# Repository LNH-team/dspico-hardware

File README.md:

# DSpico Hardware
## 🗺️ Contents
- [ℹ Introduction](#ℹ-introduction)
- [❔ About this repository](#-about-this-repository).
- [🎮 DSpico PCB](#-dspico-pcb)
- [🧰 DSpico Shell](#-dspico-shell)
- [🎨 Artwork: Stickers and box art](#-artwork-stickers-and-box-art)
- [📦 Instructions](#-instructions)
- [🛠 Development](#-development)
- [👥 Contributions](#-contributions)
- [👾 Discord](#-discord)
- [📋 LNH Team Statement](#-lnh-team-statement)
- [⚖ License](#-license)

## ℹ Introduction
### What is DSpico?
DSpico is the world's first open-source DS(i) flashcart, created by the LNH team. Everything from the PCB, shell, stickers, and box art is open-source. You can either build it yourself as a DIY project or have it made by a manufacturer.

### Features
- RP2040 microcontroller
- 16 Mbit flash memory
- Micro USB port
- Micro SD slot
- Development port
- Two LEDs (red and blue)
- Dual power support: can be powered by USB and DS simultaneously (by ORing circuit)

With the [DSpico Firmware](https://github.com/LNH-team/dspico-firmware):
- Sequential SD read speed: up to 6MB/s
- Power consuption: ~57 mW
- Compatible with DSi mode
- Compatible with [Pico Loader](https://github.com/LNH-team/pico-loader) and [Pico Launcher](https://github.com/LNH-team/pico-launcher)

## ❔ About this repository
This repository contains the necessary files for the hardware of the DSpico, including a PCB, CAD design of the shell, stickers for cartridge and box art.

## 🎮 DSpico PCB
The PCB design is located in the [`dspico-pcb`](dspico-pcb) folder. This folder contains all the necessary files for PCB fabrication, as well as the design files created using the electronic design software.

### 📂 Included Subfolders:
- [`design-files`](dspico-pcb/design-files): PCB schematic and layout of DSpico. (KiCad format)
- [`fabrication-files`](dspico-pcb/fabrication-files): Gerber files, Pick&Place files and BOM for PCB fabrication of DSpico.
- [`docs`](dspico-pcb/docs): Documentation for manufacturing and assembling DSpico.

### 🔌 Pinout

| **Peripheral**  | **Pin name - Peripheral** | **Pin name - RP2040** | **Pin number - RP2040** |
|-------------|-----------------------|-------------------|-------------|
| **DS Slot** | D0                    | GPIO12            | 15          |
|             | D1                    | GPIO13            | 16          |
|             | D2                    | GPIO14            | 17          |
|             | D3                    | GPIO15            | 18          |
|             | D4                    | GPIO16            | 27          |
|             | D5                    | GPIO17            | 28          |
|             | D6                    | GPIO18            | 29          |
|             | D7                    | GPIO19            | 30          |
|             | CLK_DS                | GPIO11            | 14          |
|             | ROM_CS                | GPIO10            | 13          |
|             | SPI_CS                | GPIO21            | 32          |
|             | IRQ                   | GPIO20            | 31          |
|             | RST_DS                | GPIO09            | 12          |
| **SD slot**| CLK_SD                | GPIO03            | 5           |
|             | DAT0                  | GPIO05            | 7           |
|             | DAT1                  | GPIO06            | 8           |
|             | DAT2                  | GPIO07            | 9           |
|             | DAT3                  | GPIO08            | 11          |
|             | CMD                   | GPIO04            | 6           |
| **DEV port**| SWD                   | SWD               | 25          |
|             | SWCLK                 | SWCLK             | 24          |
|             | TX                    | GPIO0            | 2           |
|             | RX                    | GPIO1            | 3           |
| **Blue LED**   | LED_B                 | GPIO28            | 40          |
| **Red LED**   | LED_R                 | GPIO27            | 39          |

## 🧰 DSpico Shell

The CAD design of the shell is located in the [`dspico-shell`](dspico-shell) folder. This folder contains 3D models of the shell (output 3d models and design files), which can be viewed and modified using CAD design software Autodesk Inventor

### 📂 Included Subfolders:
- [`design-files`](dspico-shell/design-files): Contains source design files for the shell
- [`3d-models`](dspico-shell/3d-models): Contains 3D models of the shell in STL and STEP format for fabrication.

## 🎨 Artwork: Stickers and box art
The stickers and box art design are located in the [`dspico-artwork-design`](dspico-artwork-design).  This folder contains stickers for cartridge and box art in SVG, PSD and PNG formats.

### 📂 Included Subfolders:
- [`stickers`](dspico-artwork-design/stickers): Stickers to print and put on your DSpico cartridge.
- [`box-art`](dspico-artwork-design/box-art): Box art design to print and put on your DS box.
- [`logo`](dspico-artwork-design/logo): DSpico logo in different formats.
- [`others`](dspico-artwork-design/others): Other graphics related to DSpico

## 📦 Instructions
### 1️⃣ Build
1. **Manufacture the PCB and Shell**<br>
    Start by producing both the PCB and the shell. Go to the respective sections, [`dspico-pcb`](dspico-pcb) and [`dspico-shell`](dspico-shell), and read the README file in each to understand how to create these parts.

2. **Optional: Customize with a Sticker and Box Art**<br>
    If desired, you can print a sticker from the stickers section and add box art [`dspico-artwork-design`](dspico-artwork-design) for storing your DSpico (for example, by reusing an existing box).

### 2️⃣ Assembly
Once you have both the PCB and the shell manufactured, the next step is to assemble them. Follow these steps:
1. First, insert the PCB into the bottom part of the shell.
2. Next, attach the top part of the shell by aligning the pegs with the holes in the bottom part.
3. Stick your favorite DSpico sticker on top part.
Make sure everything fits, and your DSpico will be ready for the next steps!

### 3️⃣ Setup the software
Follow the [guide](https://github.com/LNH-team/dspico/blob/develop/GUIDE.md) for instructions on how to compile and setup the firmware and the contents of the micro SD card.

## 🛠 Development
The DSpico features a development port for creating new applications and developing new peripherals. The available communication ports are as follows:
- UART
- I2C
- x2 GPIO
- SWD (debug)

As for the power it can provide to peripherals, it is:
- 3.3 V (up to 50 mA)

The pitch between pins of this port is 2.54 mm such that some connectors can be soldered (as long as it does not interfere with the rest of the DSpico mechanics). For example a male or female header.

## 👥 Contributions

Contributions are welcome. If you wish to improve the PCB or shell designs, feel free to submit a pull request!

### Contributors:

#### PCB:
 - [nitehack](https://www.github.com/nitehack)
 - [Gericom](https://github.com/Gericom) (first DSpico prototype)

#### Shell:
 - rcuevas
 - [nitehack](https://www.github.com/nitehack)

#### Artworks:
 - [nitehack](https://www.github.com/nitehack)

## 👾 Discord
- [DS⁽ⁱ⁾ Mode Hacking!](https://discord.gg/fCzqcWteC4)

## 📋 LNH Team Statement
We wish to make it clear that the LNH team has no affiliation with any commercial projects, and we do not endorse or engage in any for-profit endeavors concerning DSpico or related materials. This statement serves as a formal disavowal of any financial or business dealings that may arise in relation to DSpico, and we take no responsibility for any actions or transactions carried out by third parties in this regard.

## ⚖ License

This project is licensed under the CC BY-SA 4.0 License. See the [`LICENSE`](LICENSE) file for more details.

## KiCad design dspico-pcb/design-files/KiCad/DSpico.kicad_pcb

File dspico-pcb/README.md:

# DSpico PCB

This repository contains the files and configurations needed to fabricate and assemble the PCB for the **DSpico** flashcart. You can manufacture with the manufacturer you prefer. In this readme we include a guide on how to order it from [JLCPCB](https://cart.jlcpcb.com/quote?spm=Jlcpcb.Homepage.1006)

## 📂 Included Subfolders:
- [`design-files`](./design-files): PCB schematic and layout of DSpico. (KiCad format)
- [`fabrication-files`](./fabrication-files): Gerber files, Pick&Place files and BOM for PCB fabrication of DSpico.
   - 📂 `Gerber`: Gerber files required for fabrication.
   - 📂 `NC Drill`: Contains the NC Drill files required for PCB hole drilling.
   - 📂 `BOM`: Bill of Materials (BOM) for assembly.
   - 📂 `Pick Place`: Pick and Place files for component placement.
- [`docs`](./docs): Documentation for manufacturing and assembling DSpico. (including schematics)

---

## 📦 Guide to get a PCB

### 1. PCB Order- JLCPCB
> [!WARNING]
> This guide was last reviewed on **November 22, 2025**. 
> Please be aware that the manufacturer's website and production processes may have changed since this date. 

1. **Prepare files**
   - Make a compressed file ZIP of `NC Drill` and `Gerber` folder with the name of `Gerber.zip` (for example)
2. **Go to the Website of manufacturer**
  
   - Visit [JLCPCB PCB Quote](https://cart.jlcpcb.com/quote).

3. **Upload Gerber and NC Drill Files**:

   - Upload the `Gerber.zip` file to the JLCPCB configurator.

4. **PCB Configuration**

   - Base Material: **FR-4**
   - Number of Layers: **4 layers** (auto-detected after uploading Gerber files).
   - Dimensions: (auto-detected after uploading Gerber files).
   - Quantity: **5 units** (minimum)

>PCB Specifications
   - Deburring/Edge rounding: Yes
   - Different Design: 1
   - Delivery Format : Single PCB
   - PCB Thickness: **0.8mm** (very important)
   - PCB Color: (As you want but normally green is the cheapest)
   - Silkscreen: **White** 
   - Material Type: FR4 TG135
   - Surface Finish: **ENIG**
   - Gold Thickness: **1U"**. (Or more, but more expensive)

>High-spec Options
   - Outer Copper Weight: **1 oz**
   - Inner Copper weight: **0.5 oz**
   - Specify Layer Sequence: YES

   - Specify Stackup: **No**
   - Via Covering: **Plugged**
   - Min via hole size/diameter: **0.3mm (0.4/0.45mm)**
   - Board Outline Tolerance: **±0.2mm (Regular)**
   - Confirm Production File: **Yes**
   - Mark on PCB: **Remove Mark**
   - Electrical Test: **Flying Probe Fully Test**
   - Gold Fingers: **No**
   - Castellated Holes: **No**
   - Press-Fit Holes: **No**
   - Edge Plating: **No**
   - Blind Slots: **No**
   - UL Marking: **No**
   - Via Plating Method: **Not Specified** 

>PCB Remark
>
Add the next note:

**Ensure enough space is left on the edge rails for the USB connector. Leave the slot space as per the silkscreen**

If they contact you via email after placing the order about this note, attach the following image

---

### 2. PCB Assembly Order- first step - JLCPCB

1. **Assembly Type**:
   - **Assemble top side**.
   - PCBA Type: **Standard**
   - Assembly Side: **Top side**
   - PCBA Qty: **5**. (Or custom Qty)
   - Edge Rails/Fiducials: **Added by JLCPCB**
   - Confirm Parts Placement: **Yes**
   - Stencil Storage: **No**
   - Fixture Storage: **No**
   - Parts Selection: **By Customer**

2. **Advanced Options**:
   - Bake Components: **No**
   - Board Cleaning: **Yes**
   - Packaging: **Antistatic bubble film**.
   - Solder Paste: **SN96.5%, Ag3.0%, Cu0.5%(260ºC)**
   - Add paste for unpopulated pad & step stencil opening: **No**
   - Function test: **No** 
   - Photo confirmation: **No**
   - Conformal Coating (cleaning included): **No**
   - Depanel boards & edge rail before delivery: **No**
   - Flying Probe Test: **No**
   - Nitrogen reflow soldering: **No**
   - PCBA remark: **No**

3. On the **Price Summary** window, click **Next**.

---

### 3. PCB Assembly Order - second step - JLCPCB

Follow these steps to continue with the process

### Preview pcb specifications
On the **Preview PCB** page, click **Next** to proceed.  

### Add Required Files for assembly 
In the next window, upload the necessary files for your DSpico PCB:  

   1. **Add BOM File**  
      - Click on **Add BOM File**.  
      - Search for and select the Bill of Materials (BOM) file:  
        - `"Bill of Materials-DSpico.xlsx"` (Ensure it matches the version of DSpico you are building).  

   2. **Add Pick-and-Place (CPL) File**  
      - Click on **Add CPL File**.  
      - Search for and select the Pick and Place file:  
        - `"Pick Place for DSpico_PCB.csv"` (Ensure it matches the version of DSpico you are building).  

   3. Once both files are uploaded, press **Process BOM & CPL**.  

### Verify Components  
In the next window, carefully verify the components:  

1. Check that each component selected by the **JLCPCB tool** matches the corresponding part in the BOM:  
   - Use the file `"Bill of Materials-DSpico.xlsx"` for reference.  
   - Ensure the selected part is the same or a suitable alternative.  

     (The image is just a reference, please follow the components indicated in the BOM file)

> [!IMPORTANT]
> If the components do not match, there is a risk of malfunction or improper operation of the DSpico. **Double-check every part detail carefully. It's your responsibility**  

> [!TIP]  
 > JLCPCB may sometimes show certain parts as out of stock. However, other users may have that part in their accounts, which you can purchase and add to your order. If this is not an option, you can place an order for the part separately, though you’ll need to wait for JLCPCB to buy them and receive them.  After using the necessary components, you can sell your parts on your account. More info: https://jlcpcb.com/help/article/What-is-JLCPCB-Parts-Pre-order-Service
 > You can also look for an alternative to the component by clicking the magnifying-glass icon next to it and searching for a compatible replacement.

### Check Component Placement  
1. In the next window, verify the component placement:  
   - Ensure the **position**, **rotation**, and **Pin 1 orientation** are correct.  

### 3. Finalize the Process  
1. Click **Next** to proceed through the final steps of the process.  
2. Wait for JLCPCB to review your order.  
3. Review and accept their feedback before making the payment.  

--- 

## 💡 Recommendations
- We recommend using a **Hard Gold** surface finish if you can afford it. This is not possible with JLCPCB, but it is available with PCBWAY and other manufacturers. It will significantly improve the conductivity of the PCB pins, reducing detection issues with the DSpico.

## ❓ FAQ
>- Can I order just 1 PCB assembled?

Depending on the manufacturer, you may or may not be able to do this, but it will be very expensive. They usually ask for a minimum of 2 assembled PCBs. We recommend ordering 5 assembled PCBs.

>- What happens if a component of JLCPCB is out of stock? 

You must find an alternative or purchase that component from the JLCPCB library. See here for more information: https://jlcpcb.com/help/article/What-is-JLCPCB-Parts-Pre-order-Service

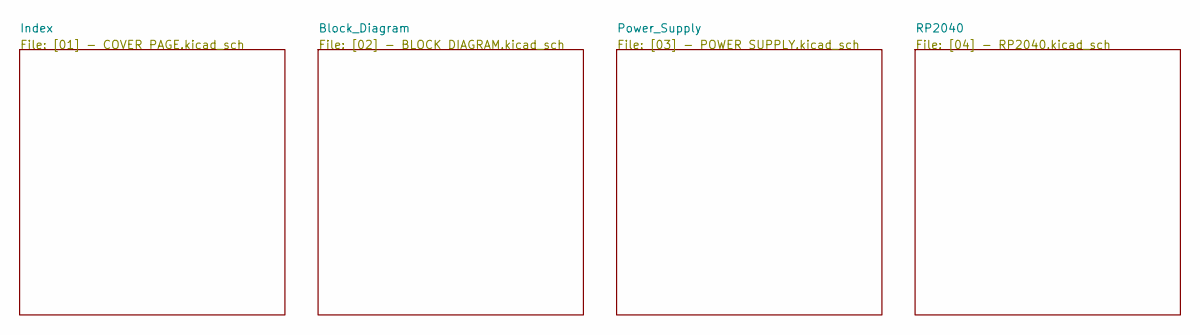
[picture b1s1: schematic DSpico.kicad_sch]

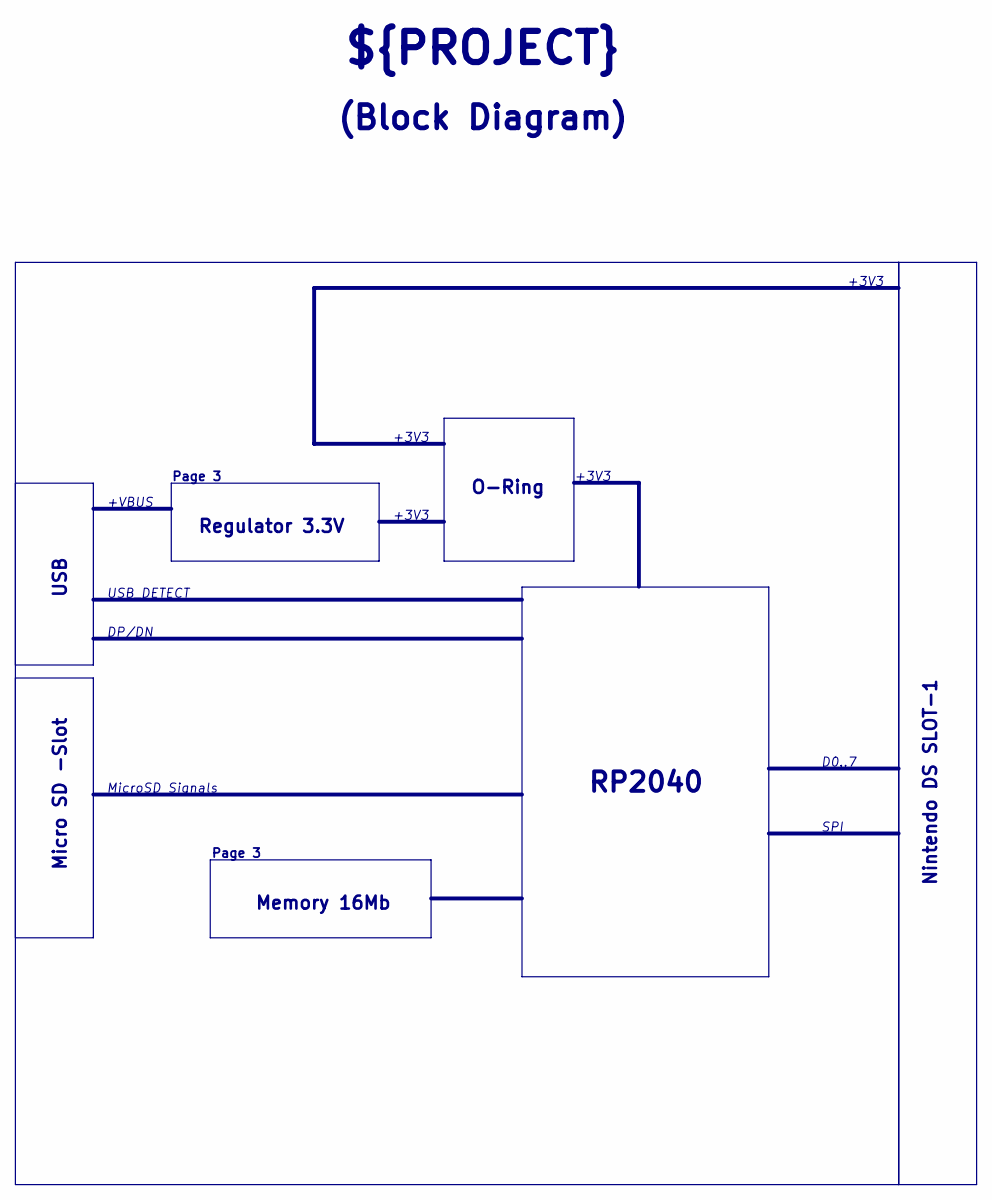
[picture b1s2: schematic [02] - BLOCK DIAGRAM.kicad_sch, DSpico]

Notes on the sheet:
+VBUS
+3V3
RP2040
Page 3
(Block Diagram)
USB_DETECT
D0..7
SPI
O-Ring
USB
MicroSD Signals
Regulator 3.3V
Nintendo DS SLOT-1
DP/DN
${PROJECT}
Micro SD -Slot
Memory 16Mb

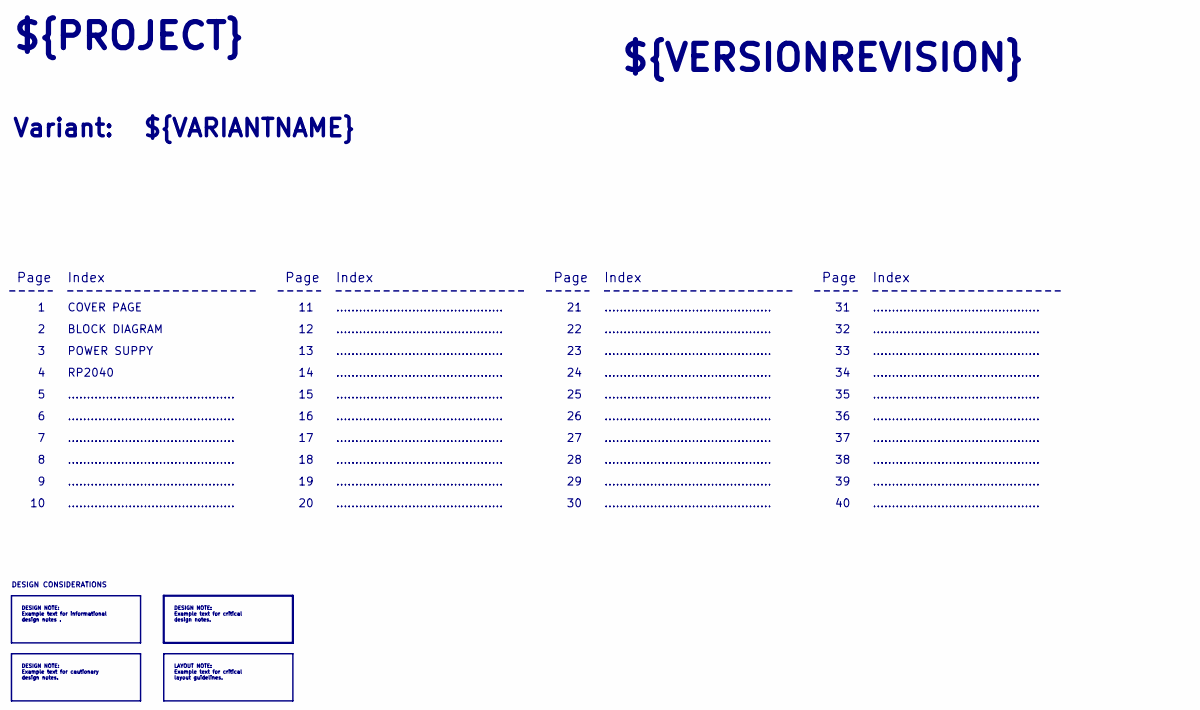
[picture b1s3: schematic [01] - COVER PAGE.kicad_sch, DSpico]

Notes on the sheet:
Page
............................................
POWER SUPPY
COVER PAGE
${VARIANTNAME}
Index
BLOCK DIAGRAM
${PROJECT}
DESIGN CONSIDERATIONS
RP2040
${VERSIONREVISION}
Variant:
DESIGN NOTE: Example text for cautionary design notes.
DESIGN NOTE: Example text for informational design notes .
DESIGN NOTE: Example text for critical design notes.
LAYOUT NOTE: Example text for critical layout guidelines.

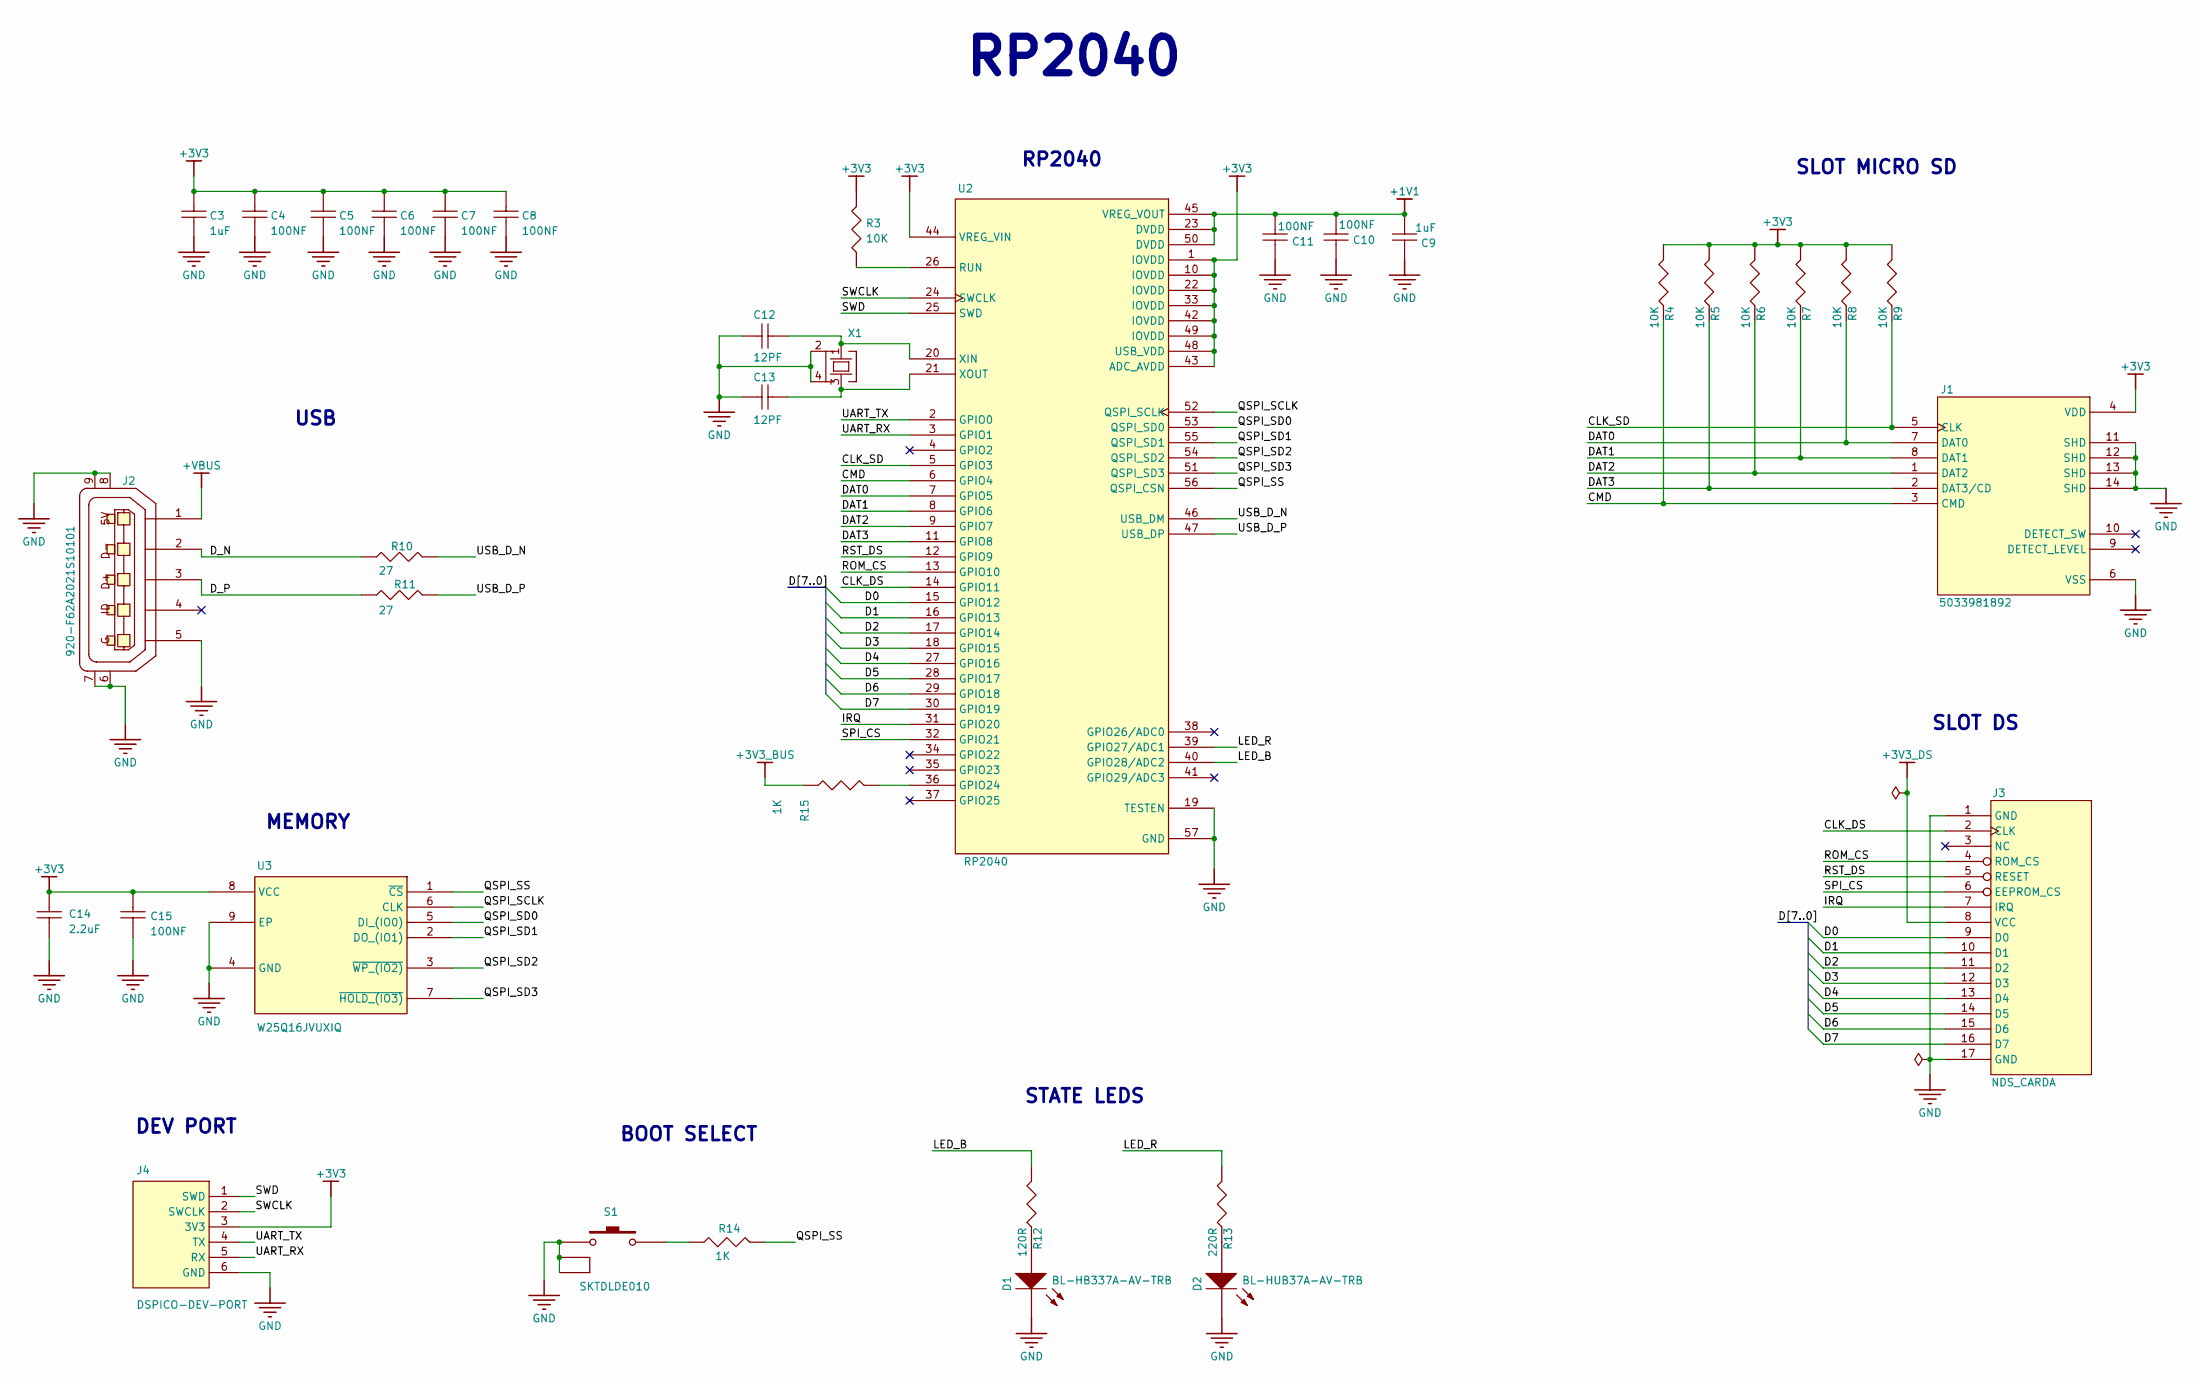
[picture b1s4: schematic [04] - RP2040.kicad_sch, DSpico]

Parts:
C3, C9: 1uF; C0402; TOLERANCE 10%; VOLTAGE RATING 25V; MANUFACTURER PART NUMBER C1005X5R1E105K050BC
C4, C5, C6, C7, C8, C10, C11, C15: 100NF; C0402; TOLERANCE 10%; VOLTAGE RATING 16V; MANUFACTURER PART NUMBER GRM155R71C104KA88D
C12, C13: 12PF; C0402; TOLERANCE 5%; VOLTAGE RATING 50V; MANUFACTURER PART NUMBER 04025A120JAT2A
C14: 2.2uF; C0402; MANUFACTURER PART NUMBER C1005X5R1A225K050BC
D1: BL-HB337A-AV-TRB; LED0402-RD; FORWARD VOLTAGE 2.8V; MANUFACTURER PART NUMBER BL-HB337A-AV-TRB
D2: BL-HUB37A-AV-TRB; LED0402-RD; FORWARD VOLTAGE 2V; MANUFACTURER PART NUMBER BL-HUB37A-AV-TRB
J1: 5033981892; 503398-1892_MOL
J2: 920-F62A2021S10101; MICRO-USB_MICRO-USB-31
J3: NDS_CARDA; NDS_CARD
J4: DSPICO-DEV-PORT; EP_DEV_PORT; CURRENT RATING ?; VOLTAGE RATING 3.3V; MANUFACTURER PART NUMBER PICO-DEVELOP-PORT
R3, R4, R5, R6, R7, R8, R9: 10K; R0402; TOLERANCE 1%; POWER RATING 63mW; MANUFACTURER PART NUMBER CRCW040210K0FKED
R10, R11: RC0402FR-0727RL; R0402; WORKING VOLTAGE 50V; TOLERANCE 1%
R12: 120R; R0402; VOLTAGE RATING 50V; POWER RATING 62.5mW; MANUFACTURER PART NUMBER RC0402FR-07120RL
R13: 220R; R0402; VOLTAGE RATING 50V; POWER RATING 62.5mW; MANUFACTURER PART NUMBER RC0402FR-07220RL
R14, R15: 1K; R0402; TOLERANCIA DE RESISTENC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 ± 1%; MANUFACTURER PART NUMBER CRCW04021K00FKED
S1: SKTDLDE010; KEY-SMD_SKTDLDE010; MANUFACTURER PART NUMBER SKTDLDE010
U2: RP2040; QFN40P700X700X90-57N
U3: W25Q16JVUXIQ; SON50P300X200X60-9N
X1: XYDBPCNANF-12MHZ; OSC-SMD_4P-L2.5-W2.0-BL

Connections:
+1V1: C9.2, C10.2, C11.2, U2.23 (DVDD), U2.45 (VREG_VOUT), U2.50 (DVDD)
+3V3: C3.2, C4.2, C5.2, C6.2, C7.2, C8.2, C14.2, C15.2, J1.4 (VDD), J4.3 (3V3), R3.2, R4.2, R5.2, R6.2, R7.2, R8.2, R9.2, U2.1 (IOVDD), U2.10 (IOVDD), U2.22 (IOVDD), U2.33 (IOVDD), U2.42 (IOVDD), U2.43 (ADC_AVDD), U2.44 (VREG_VIN), U2.48 (USB_VDD), U2.49 (IOVDD), U3.8 (VCC); also elsewhere on the board
+3V3_BUS: R15.1; also elsewhere on the board
+3V3_DS: J3.8 (VCC); also elsewhere on the board
+VBUS: J2.1; also elsewhere on the board
/RP2040/CLK_DS: J3.2 (CLK), U2.14 (GPIO11)
/RP2040/CLK_SD: J1.5 (CLK), R9.1, U2.5 (GPIO3)
/RP2040/CMD: J1.3 (CMD), R4.1, U2.6 (GPIO4)
/RP2040/D0: J3.9 (D0), U2.15 (GPIO12)
/RP2040/D1: J3.10 (D1), U2.16 (GPIO13)
/RP2040/D2: J3.11 (D2), U2.17 (GPIO14)
/RP2040/D3: J3.12 (D3), U2.18 (GPIO15)
/RP2040/D4: J3.13 (D4), U2.27 (GPIO16)
/RP2040/D5: J3.14 (D5), U2.28 (GPIO17)
/RP2040/D6: J3.15 (D6), U2.29 (GPIO18)
/RP2040/D7: J3.16 (D7), U2.30 (GPIO19)
/RP2040/DAT0: J1.7 (DAT0), R8.1, U2.7 (GPIO5)
/RP2040/DAT1: J1.8 (DAT1), R7.1, U2.8 (GPIO6)
/RP2040/DAT2: J1.1 (DAT2), R6.1, U2.9 (GPIO7)
/RP2040/DAT3: J1.2 (DAT3/CD), R5.1, U2.11 (GPIO8)
/RP2040/D_N: J2.2, R10.1
/RP2040/D_P: J2.3, R11.1
/RP2040/IRQ: J3.7 (IRQ), U2.31 (GPIO20)
/RP2040/LED_B: R12.2, U2.40 (GPIO28/ADC2)
/RP2040/LED_R: R13.2, U2.39 (GPIO27/ADC1)
/RP2040/QSPI_SCLK: U2.52 (QSPI_SCLK), U3.6 (CLK)
/RP2040/QSPI_SD0: U2.53 (QSPI_SD0), U3.5 (DI_(IO0))
/RP2040/QSPI_SD1: U2.55 (QSPI_SD1), U3.2 (DO_(IO1))
/RP2040/QSPI_SD2: U2.54 (QSPI_SD2), U3.3 (~WP_(IO2))
/RP2040/QSPI_SD3: U2.51 (QSPI_SD3), U3.7 (~HOLD_(IO3))
/RP2040/QSPI_SS: R14.2, U2.56 (QSPI_CSN), U3.1 (~CS)
/RP2040/ROM_CS: J3.4 (ROM_CS), U2.13 (GPIO10)
/RP2040/RST_DS: J3.5 (RESET), U2.12 (GPIO9)
/RP2040/SPI_CS: J3.6 (EEPROM_CS), U2.32 (GPIO21)
/RP2040/SWCLK: J4.2 (SWCLK), U2.24 (SWCLK)
/RP2040/SWD: J4.1 (SWD), U2.25 (SWD)
/RP2040/UART_RX: J4.5 (RX), U2.3 (GPIO1)
/RP2040/UART_TX: J4.4 (TX), U2.2 (GPIO0)
/RP2040/USB_D_N: R10.2, U2.46 (USB_DM)
/RP2040/USB_D_P: R11.2, U2.47 (USB_DP)
GND: C3.1, C4.1, C5.1, C6.1, C7.1, C8.1, C9.1, C10.1, C11.1, C12.1, C13.1, C14.1, C15.1, D1.1, D2.1, J1.6 (VSS), J1.11 (SHD), J1.12 (SHD), J1.13 (SHD), J1.14 (SHD), J2.5, J2.6, J2.7, J2.8, J2.9, J3.1 (GND), J3.17 (GND), J4.6 (GND), S1.1, S1.3, S1.4, U2.19 (TESTEN), U2.57 (GND), U3.4 (GND), U3.9 (EP), X1.2, X1.4; also elsewhere on the board
unnamed: D1.2, R12.1
unnamed: D2.2, R13.1
unnamed: R14.1, S1.2
unnamed: R15.2, U2.36 (GPIO24)
unnamed: R3.1, U2.26 (RUN)
unnamed: C12.2, U2.20 (XIN), X1.1
unnamed: C13.2, U2.21 (XOUT), X1.3

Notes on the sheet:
SLOT MICRO SD
MEMORY
BOOT SELECT
RP2040
SLOT DS
STATE LEDS
DEV PORT
USB

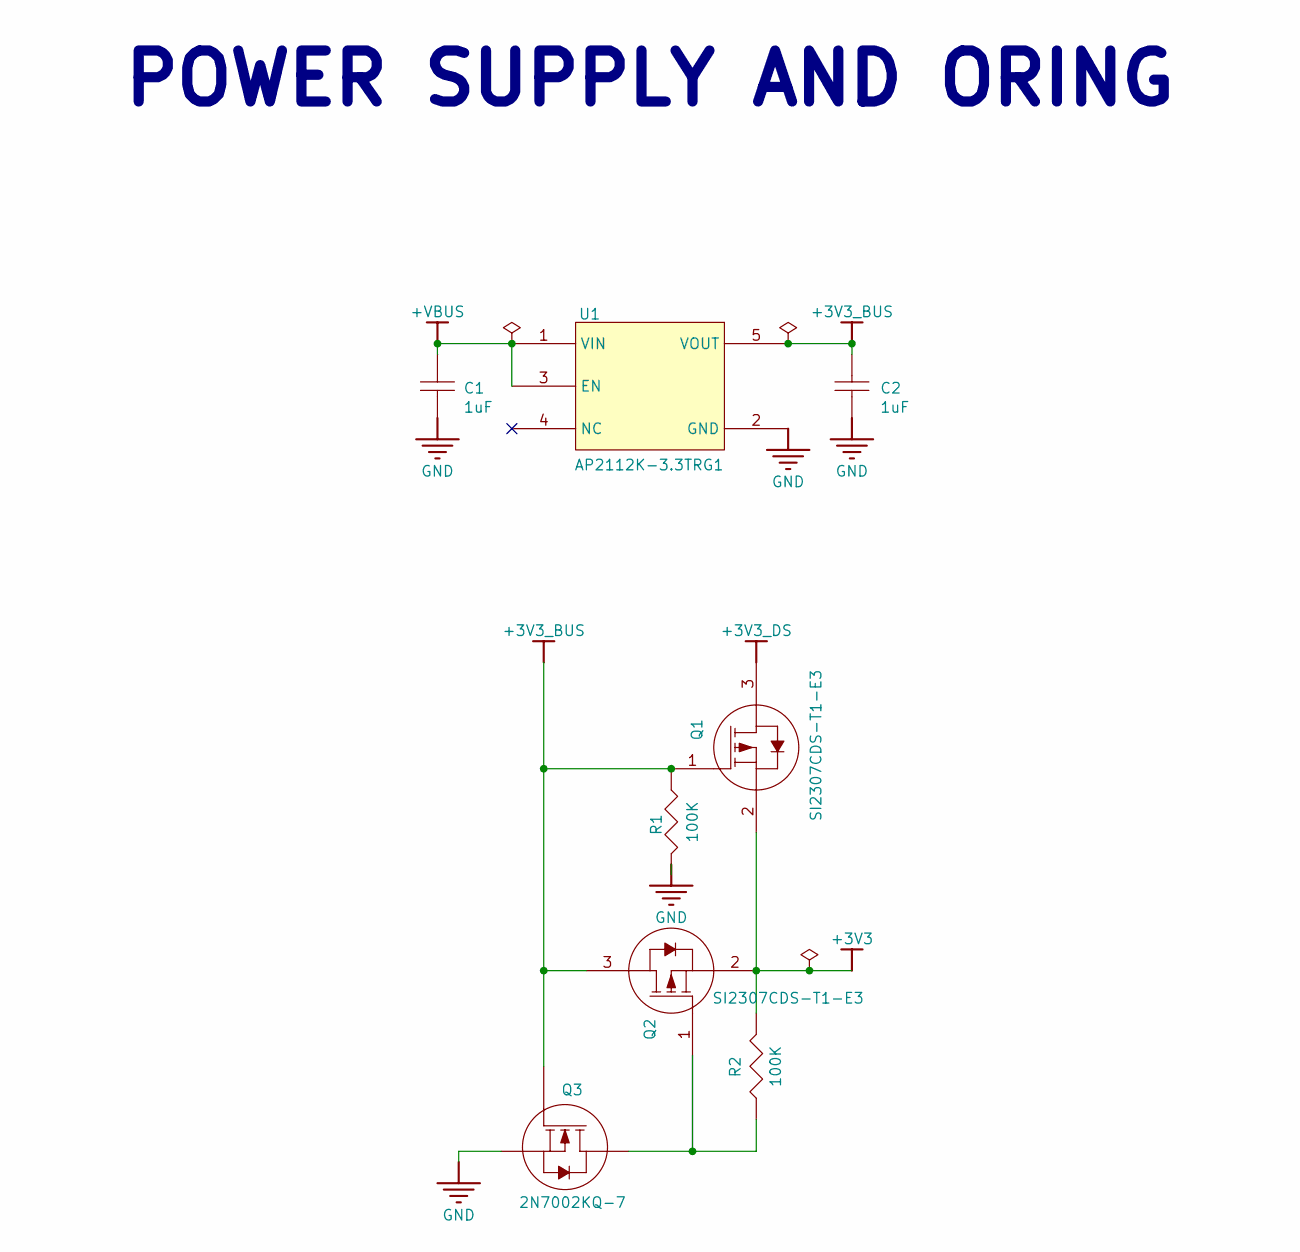
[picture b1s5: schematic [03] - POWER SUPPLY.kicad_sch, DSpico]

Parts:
C1, C2: 1uF; C0402; TOLERANCE 10%; VOLTAGE RATING 25V; MANUFACTURER PART NUMBER C1005X5R1E105K050BC
Q1, Q2: SI2307CDS-T1-E3; SOT-23_L2.9-W1.3-P1.90-LS2.4-BR
Q3: 2N7002KQ-7; SOT-23_L2.9-W1.3-P1.90-LS2.4-BR; MANUFACTURER PART NUMBER 2N7002KQ-7
R1, R2: 100K; R0402; TOLERANCE 1%; POWER RATING 63mW; MANUFACTURER PART NUMBER CRCW0402100KFKED
U1: AP2112K-3.3TRG1; SOT95P285X140-5N; DROPOUT VOLTAGE 250mV; OUTPUT VOLTAGE 3.3V; MANUFACTURER PART NUMBER AP2112K-3.3TRG1

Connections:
+3V3: Q1.2 (S), Q2.2 (S), R2.2; also elsewhere on the board
+3V3_BUS: C2.2, Q1.1 (G), Q2.3 (D), Q3.1 (G), R1.1, U1.5 (VOUT); also elsewhere on the board
+3V3_DS: Q1.3 (D); also elsewhere on the board
+VBUS: C1.2, U1.1 (VIN), U1.3 (EN); also elsewhere on the board
GND: C1.1, C2.1, Q3.2 (S), R1.2, U1.2 (GND); also elsewhere on the board
unnamed: Q2.1 (G), Q3.3 (D), R2.1

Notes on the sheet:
POWER SUPPLY AND ORING

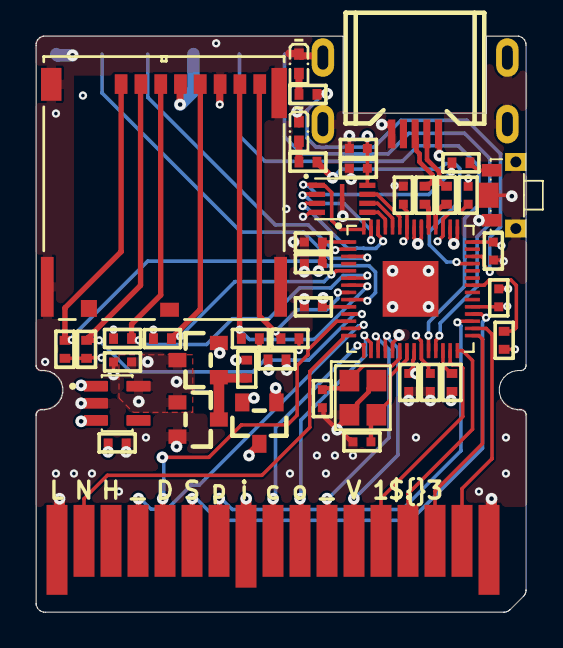
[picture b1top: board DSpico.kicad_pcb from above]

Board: 4 copper layers, 27.2 x 32.0 mm, 44 parts (1 on the bottom side), 49 nets.

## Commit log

2025-11-25 Updated readme to refer to the guide
2025-11-27 chore: Fix typo in dspico-pcb/README.md
2026-01-31 Added extra pegs
2026-04-10 Add KiCad design files for DSpico v1.3
